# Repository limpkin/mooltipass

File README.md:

Mooltipass Project Repository
=============================

This is the GitHub repository dedicated to the Mooltipass device family. It contains all the resources that were used and made for this community-driven product line since the project was first started back in December 2013.  
The Mooltipass Mini device is available for purchase <b><a href="https://www.tindie.com/products/stephanelec/mooltipass-mini-offline-password-keeper/">on our Tindie store</a></b>.  

What is the Mooltipass Project?
-------------------------------
With time, logins and passwords have become critical elements we need to remember to access the different websites and services we use daily. If we want to achieve good security, each of these credential sets should be unique.  
We therefore created the Mooltipass, a physical password keeper that remembers and encrypts your credentials so you don't have to. With this device, you can generate and safely store long and complex passwords. A personal PIN locked smartcard allows the decryption of your credentials and ensures that only you have access to them. Simply visit a website and the device will ask for your confirmation to enter your credentials when login is required.  
The Mooltipass is a standalone device connected through USB, is completely driver-less and is compatible with all major operating systems on PCs, Macs and Smartphones. It therefore is extremely simple to use our device: - Plug the Mooltipass to your computer/tablet/phone, no driver installation required.  
- Insert your smart card, unlock it with your PIN. Without the PIN, the card is useless.  
- Visit the website that needs a login. If using our browser plugin the Mooltipass asks your permission to send the stored name and password or asks you to save/generate new credentials if you are logging in for the first time.  
- If you are not using the browser plugin or logging in to something other than a web browser, you can manually tell MP to send the correct name and password. It will type it in for you, just like a keyboard. In this way, it can be used anywhere.    

Advantages over software-based solutions
----------------------------------------
A software-based password keeper uses a passphrase to decrypt a credentials database located inside a device (computer, smartphone...). As at a given moment, your passphrase and your database are stored inside your device's memory, a malicious program with access to both elements could <b><a href="http://thehackernews.com/2014/11/new-citadel-trojan-targets-your.html">compromise all your passwords at once</a></b>. In some cases, security flaws of software-based solutions can also lead to entire unencrypted databases being extracted by <b><a href="http://www.theregister.co.uk/2016/07/27/zero_day_hole_can_pwn_millions_of_lastpass_users_who_visit_a_site">visiting a simple website</a></b>.  
We therefore offer the following advantages:  
- **Stronger security**: we reduce the number of attack vectors by basically having our device type your passwords for you. 
- A **non-proprietary device**: as our product is open anyone can develop new tools for it. There will never be fees for the services we offer.  
- An **open-source platform**: all our source code can be viewed, allowing you to check that your credentials are only kept inside the device and not leaked to the outside  
- A **trusted platform**: as only our tested source code is running on the Mooltipass, there can't be any viruses or malicious programs compromising your stored credentials  

The Platform
------------
The Mooltipass is composed of the main device shown above and a smart card.  
On the device are stored your AES-256 encrypted credentials. The smart card is a read protected memory that needs a PIN code to unlock its contents (AES-256 key + a few websites credentials). As with your chip and pin card, too many tries will permanently lock the smart card.

The Firmware
------------
**We want the device to be as simple as possible.** Ideally, the end user shouldn't have to spend more than a few seconds to use its basic functionalities.  
A browser extension runs on the user's computer and sends the current website to the Mooltipass. When the user has to log in, the Mooltipass will light up and ask for confirmation to enter the credentials.

Data Safety
-----------
Safety is a primary concern for the Mooltipass development team, which is why we offer several **secure** ways to backup your credentials.  
The smart card containing the AES key used for encrypting the passwords can be **cloned** using the Mooltipass, copying its PIN code as well. The encrypted credentials stored in the Mooltipass internal flash can be **exported** to the official Mooltipass website or simply somewhere on your local computer.

A Brief History of Security Flaws and Breaches
----------------------------------------------
We often think that the devices and websites we use are exempt from security flaws.  
You may see **if one of your accounts has already been compromised** by visiting <b><a href="https://haveibeenpwned.com/">this website</a></b>.  
We also compiled a brief list of major security breaches and vulnerabilities found during the last few months: 
- 01/2018 <a href="https://yro.slashdot.org/story/18/01/29/182210/lenovos-fingerprint-scanner-can-be-bypassed-via-a-hardcoded-password">
Lenovo's Fingerprint Scanner Can Be Bypassed via a Hardcoded Password </a>
- 12/2017 <a href="https://it.slashdot.org/story/17/12/17/0329223/windows-10-bundled-a-password-manager-with-a-security-flaw">Windows 10 Bundled a Password Manager with a Security Flaw </a>
- 09/2017 <a href="https://arstechnica.com/information-technology/2017/09/bluetooth-bugs-open-billions-of-devices-to-attacks-no-clicking-required/">Billions of devices imperiled by new clickless Bluetooth attack</a>
- 09/2017 <a href="https://techcrunch.com/2017/09/07/equifax-data-leak-could-involve-143-million-consumers/">Equifax data leak involves 143 million consumers</a>
- 08/2017 <a href="https://blog.quarkslab.com/vulnerabilities-in-high-assurance-boot-of-nxp-imx-microprocessors.html">Vulnerabilities in High Assurance Boot of NXP i.MX microprocessors</a>
- 08/2017 <a href="https://it.slashdot.org/story/17/08/01/206234/hackers-can-turn-amazon-echo-into-a-covert-listening-device">Hackers Can Turn Amazon Echo Into a Covert Listening Device</a>
- 07/2017 <a href="https://tech.slashdot.org/story/17/07/18/2039238/flaw-in-iot-security-cameras-leaves-millions-of-devices-open-to-hackers">Flaw In IoT Security Cameras Leaves Millions of Devices Open To Hackers</a>
- 07/2017 <a href="https://blog.exodusintel.com/2017/07/26/broadpwn/">**1 billion** smartphones can be compromised due to a flaw in BCM43XX chipsets</a>
- 07/2017 <a href="https://it.slashdot.org/story/17/07/03/0343258/severe-systemd-bug-allowed-remote-code-execution-for-two-years">Severe Systemd Bug Allowed Remote Code Execution For Two Years</a>
- 06/2017 <a href="https://it.slashdot.org/story/17/06/24/1825235/researcher-finds-critical-openvpn-bug-using-fuzzing">Researcher Finds Critical OpenVPN Bug Using Fuzzing</a>
- 06/2017 <a href="https://it.slashdot.org/story/17/06/23/1943245/wikileaks-doc-dump-reveals-cia-tools-for-hacking-air-gapped-pcs">WikiLeaks Doc Dump Reveals CIA Tools For Hacking Air-Gapped PCs</a>
- 06/2017 <a href="http://www.zdnet.com/article/zero-day-skype-flaw-causes-crashes-remote-code-execution/">Zero-day Skype flaw causes crashes, remote code execution</a>
- 06/2017 <a href="https://arstechnica.com/security/2017/06/advanced-cia-firmware-turns-home-routers-into-covert-listening-posts/">Advanced CIA firmware has been infecting Wi-Fi routers for years</a>
- 06/2017 <a href="http://www.zdnet.com/article/onelogin-hit-by-data-breached-exposing-sensitive-customer-data/">Password manager OneLogin hacked, exposing sensitive customer data</a>
- 05/2017 <a href="http://www.zdnet.com/pictures/biggest-hacks-leaks-and-data-breaches-2017/2/">2017 biggest hacks: Bell Canada, Edmodo, HipChat, Wonga, DaFont, PoliceOne hacked</a>
- 05/2017 <a href="http://www.wired.co.uk/article/kodi-vlc-subtitles-hack-risk-security">Kodi and VLC users at risk of viruses hidden in subtitles</a>
- 05/2017 <a href="https://hardware.slashdot.org/story/17/05/07/2034245/intels-remote-hijacking-flaw-was-worse-than-anyone-thought">Intel AMT bug that allows hackers to remotely gain administrative control over huge fleets of computers without entering a password</a>
- 03/2017 <a href="https://it.slashdot.org/story/17/03/19/0126257/edge-vmware-safari-and-ubuntu-linux-hacked-at-pwn2own-2017">Edge, VMWare, Safari, And Ubuntu Linux Hacked at Pwn2Own 2017</a>
- 03/2017 <a href="https://wikileaks.org/ciav7p1/">Vault 7: CIA Hacking Tools Revealed</a> : "These techniques permit the CIA to bypass the encryption of WhatsApp, Signal, Telegram, Wiebo, Confide and Cloackman by hacking the "smart" phones that they run on and collecting audio and message traffic before encryption is applied."
- 03/2017 <a href="https://it.slashdot.org/story/17/03/06/1838223/huge-database-leak-reveals-137-billion-email-addresses-and-exposes-illegal-spam-operation">Huge Database Leak Reveals 1.37 Billion Email Addresses and Exposes Illegal Spam Operation</a>
- 02/2017 <a href="https://it.slashdot.org/story/17/02/24/0319243/cloudflare-leaks-sensitive-user-data-across-the-web">Cloudflare Leaks Sensitive User Data Across the Web</a>
- 01/2017 <a href="https://www.schneier.com/blog/archives/2017/02/cryptkeeper_bug.html">Cryptkeeper Bug: the single-character decryption key "p" decrypts everything</a>
- 01/2017 <a href="https://it.slashdot.org/story/17/01/31/1425259/netgear-exploit-found-in-31-models-lets-hackers-turn-your-router-into-a-botnet">Netgear Exploit Found in 31 Models Lets Hackers Turn Your Router Into a Botnet</a>
- 01/2017 <a href="http://arstechnica.co.uk/security/2017/01/google-plugs-severe-android-bootmode-vulnerability/">Google plugs severe Android bootmode vuln that exposed devices to spying</a>
- 12/2016 <a href="https://linux.slashdot.org/story/16/12/16/0229207/zero-days-hitting-fedora-and-ubuntu-open-desktops-to-a-world-of-hurt">Zero-Days Hitting Fedora and Ubuntu Open Desktops To a World of Hurt </a>
- 12/2016 <a href="https://techcrunch.com/2016/12/14/yahoo-discloses-hack-of-1-billion-accounts/">Yahoo discloses hack of 1 billion accounts</a>
- 12/2016 <a href="https://it.slashdot.org/story/16/12/13/1611243/malware-found-in-the-firmware-of-26-low-cost-android-models">Malware Found In the Firmware of 26 Low-Cost Android Models </a>
- 11/2016 <a href="https://tech.slashdot.org/story/16/11/30/1720202/more-than-1-million-android-devices-rooted-by-gooligan-malware">More Than 1 Million Android Devices Rooted By Gooligan Malware</a>
- 11/2016 <a href="https://it.slashdot.org/story/16/11/20/0043259/second-chinese-firm-in-a-week-found-hiding-a-backdoor-in-android-firmware">Second Chinese Firm In a Week Found Hiding a Backdoor In Android Firmware </a>
- 10/2016 <a href="https://news.slashdot.org/story/16/10/24/2232220/rowhammer-attack-can-now-root-android-devices">Rowhammer Attack Can Now Root Android Devices</a>
- 10/2016 <a href="https://it.slashdot.org/story/16/10/24/1356255/china-electronics-firm-to-recall-some-us-products-after-hacking-attack">China Electronics Firm To Recall Some US Products After Hacking Attack </a>
- 10/2016 <a href="https://news.slashdot.org/story/16/10/13/2059232/android-devices-that-contain-foxconn-firmware-may-have-a-secret-backdoor">Android Devices That Contain Foxconn Firmware May Have a Secret Backdoor </a>
- 09/2016 <a href="https://it.slashdot.org/story/16/09/26/1942208/as-we-speak-teen-social-site-is-leaking-millions-of-plaintext-passwords">As We Speak, Teen Social Site Is Leaking Millions Of Plaintext Passwords </a>
- 09/2016 <a href="https://it.slashdot.org/story/16/09/22/095255/yahoo-confirms-massive-data-breach-500-million-users-impacted-updated">Yahoo Confirms Massive Data Breach, 500 Million Users Impacted</a>  
- 09/2016 <a href="https://yro.slashdot.org/story/16/09/24/0548206/97-of-the-top-companies-have-leaked-credentials-online">97% of the Top Companies Have Leaked Credentials Online</a>  
- 09/2016 <a href="https://it.slashdot.org/story/16/09/26/1942208/as-we-speak-teen-social-site-is-leaking-millions-of-plaintext-passwords">As We Speak, Teen Social Site Is Leaking Millions Of Plaintext Passwords</a>  
- 06/2016 <a href="http://www.independent.co.uk/life-style/gadgets-and-tech/news/ios-933-iphone-users-urged-to-update-after-apple-fixes-huge-password-vulnerability-a7149851.html">iOS bug allows attackers to gain full remote access to an iPhone by sending a simple iMesssage</a>  
- 06/2016 <a href="http://www.theregister.co.uk/2016/06/01/teamviewer_mass_breach_report/">Teamviewer hacked, users' Paypal account drained</a>  
- 06/2016 <a href="https://yro.slashdot.org/story/16/06/16/2035205/github-presses-big-red-password-reset-button-after-third-party-breach">GitHub Presses Big Red Password Reset Button After Third-Party Breach </a>  
- 05/2016 <a href="https://it.slashdot.org/story/16/05/27/1845202/hackers-claim-to-have-427-million-myspace-passwords">Hackers Claim to Have 427 Million Myspace Passwords</a>  
- 05/2016 <a href="https://it.slashdot.org/story/16/05/30/1227252/hackers-stole-65-million-passwords-from-tumblr">Hackers Stole 65 Million Passwords From Tumblr</a>  
- 06/2016 <a href="https://techcrunch.com/2016/06/08/twitter-hack/">Passwords for 32M Twitter accounts may have been hacked and leaked</a>  
- 06/2016 <a href="https://bits-please.blogspot.fr/2016/06/extracting-qualcomms-keymaster-keys.html">Android Full Disk Encryption Can Be Broken</a>  
- 07/2016 <a href="https://labs.bitdefender.com/2016/07/new-mac-backdoor-nukes-os-x-systems/">New Backdoor Allows Full Access to Mac Systems</a>  
- 08/2016 <a href="http://arstechnica.com/security/2016/08/qualcomm-chip-flaws-expose-900-million-android-devices/">Qualcomm security flaw allows a malicious app to gain root access</a>  
- 06/2016 <a href="https://it.slashdot.org/story/16/08/13/0325204/new-cache-attack-can-monitor-keystrokes-on-android-phones">New Cache Attack Can Monitor Keystrokes On Android Phones </a>  
- 03/2016 <a href="https://bogner.sh/2016/03/mitm-attack-against-keepass-2s-update-check/">MitM Attack against KeePass 2’s Update Check</a>  
- 07/2016 <a href="https://it.slashdot.org/story/16/07/08/2011205/apple-devices-held-for-ransom-rumors-claim-40m-icloud-accounts-hacked-apple-related-forums-compromised">Rumors Claim 40M iCloud Accounts Hacked; Apple-Related Forums Compromised</a>  
- 06/2016 <a href="http://www.theregister.co.uk/2016/07/27/zero_day_hole_can_pwn_millions_of_lastpass_users_who_visit_a_site/">Lastpass: remote 'complete account compromise' possible</a>  
- 08/2016 <a href="http://mashable.com/2016/08/26/iphone-malware-platform-secure">iPhone malware that steals your data is a reminder no platform is ever safe</a>  

Frequently Asked Questions
--------------------------

**Is your solution better than a piece of paper?**  
A piece of paper contains passwords that can easily be read when you are not paying attention to it. The Mooltipass stores encrypted passwords that can only be read when providing your PIN code.  

**If I only need to remember a PIN code, does it mean the Mooltipass is not safe?**  
Not at all, as the Mooltipass system is exactly like your chip and pin card: 3 false tries will permanently block the smart card and make credential decryption impossible.  

**Why do I need different passwords for different websites?**  
Web sites are compromised on a daily basis. If you are using the same password for different websites, one attacker could use a password he discovered on all of them.

**Why do you need an OLED screen?**  
An offline password keeper needs to provide a way to prevent *impersonation*. The user has to check that the website/service he's approving the credential sending for is the same that the website/service he's currently visiting/using, as a malicious program could emit forged requests. Moreover, having a display allows the user to operate the Mooltipass without the browser plugin using our dedicated touch interface.  
  
**Why are you using both a smart card and a main Mooltipass device?**  
There are many reasons, the main one being that it is much easier to carry a smart card around than any other object. This smart card is a secure element that contains your credentials' encryption key, it is cheap and may be cloned without compromising the system security.   
  
**What if I lose my smartcard?**  
Our device is shipped with two smart cards, so you can keep your copy somewhere safe. The Mooltipass, therefore, allows the user to clone his smartcard as many times as he wants, provided that the card PIN is correctly entered.  

**Can the smart card be used with multiple Mooltipass?**  
You can synchronize your credentials between multiple devices. This allows you to have one Mooltipass at work and one at home.  
  
**What if I lose my Mooltipass device?**  
Your encrypted credentials can be exported to either your computer or the Mooltipass official website. If you lose your device, you may purchase another one and restore your credentials.  

**Are you sure about your encryption implementation?**  
The AES-256 used in the Mooltipass has been compared again standard Nessie test vectors for correctness. Moreover, our security chain has been checked by qualified individuals.  
  
**Can I use it on Windows/Linux/Mac?**  
Yes, as no drivers are required to use the Mooltipass. It is recognized as a standard USB keyboard that will enter passwords for you.    
**Can I use on my computer/laptop/phone/tablet...?**  
Most (if not all) devices (including smartphones and tablet PCs) include a USB host capable port. The Mooltipass will work with all of them.  

**How secure is the Mooltipass?**  
We are using the most secure encryption algorithms and designed our case to make physical tampering practically impossible. Our solution is therefore perfectly suited for individuals wanting to improve their credentials safety.  

**Are you planning to make a wireless version?**  
The Mooltipass isn't wireless to skip the added costs of a lithium-ion battery and a wireless interface. Customer survey also let us know that having a USB cable wasn't a problem for most use cases.  

**How are the credentials sent to the computer?**  
The Mooltipass is enumerated as a composite HID keyboard / HID proprietary device. The credentials are sent over the HID proprietary channel when using the browser plugin and over the keyboard channel when using the Mooltipass through its touch interface.

**Is it still possible to sniff the passwords sent over HID?**  
In theory yes. As mentioned in our project description the Mooltipass aims at reducing the number of attack vectors to a minimum: the device basically types your password as if you were doing it yourself. Perfect security could only be achieved by sharing dedicated secrets with every possible service and website... which is practically impossible to do.

**If I can export my encrypted credentials, does this mean someone could crack them?**  
In short, no. We are using AES-256 encryption in CTR mode, brute-forcing the encrypted credentials takes more than fifty years.  

**If it is open source, does it mean it is less secure?**  
Not at all. Having our code open source allows everyone to check our security implementation, which actually leads to a better code quality and more trust from our final users.

Contact us
----------
You may contact the development team via <a href="https://groups.google.com/forum/?hl=en#!forum/Mooltipass">the official Google group</a> or ask for support at support[at]themooltipass[dot]com

Thanks and Acknowledgement
--------------------------
None of this would have been possible without the help of many people located all over the globe.  
Here is a nonexhaustive list:
- Darran H. (graphics, plugin, comms, general development and more) - New Zealand
- Pierre C. (GUI, encryption implementation supervision, pen testing) - France
- Bjorn W. (GUI, graphics, wise man, project advisor) - Canada
- Raoul H. (cross-platform daemon, browser extensions - France
- Henryk P. (encryption implementation supervision) - Unknown
- Olivier G. (mechanics, project advisor) - Switzerland
- Josh W. (mechanics, plugin, fw supervision) - USA
- Eric E. (schematics & layout verification) - USA
- Mike N. (flash storage, node management) - USA
- Charles E. (legal, project advisor) - USA
- Miguel A. (AES encryption, RNG) - Spain
- Tom V. (part of USB) - South Africa
- Erik M. (IRC, general help) - USA
- Mikael A. (GUI, plugin) - Sweden
- Hans N. (general help) - Denmark

Device History
--------------
1) Mooltipass Standard  
You may find all the articles detailing the Mooltipass Standard different life steps using <a href="http://hackaday.com/tag/developed-on-hackaday/">this link</a>.  
Our <a href="https://www.indiegogo.com/projects/mooltipass-open-source-offline-password-keeper">crowdfunding campaign</a> achieved its goal by raising around $125k in December 2014.

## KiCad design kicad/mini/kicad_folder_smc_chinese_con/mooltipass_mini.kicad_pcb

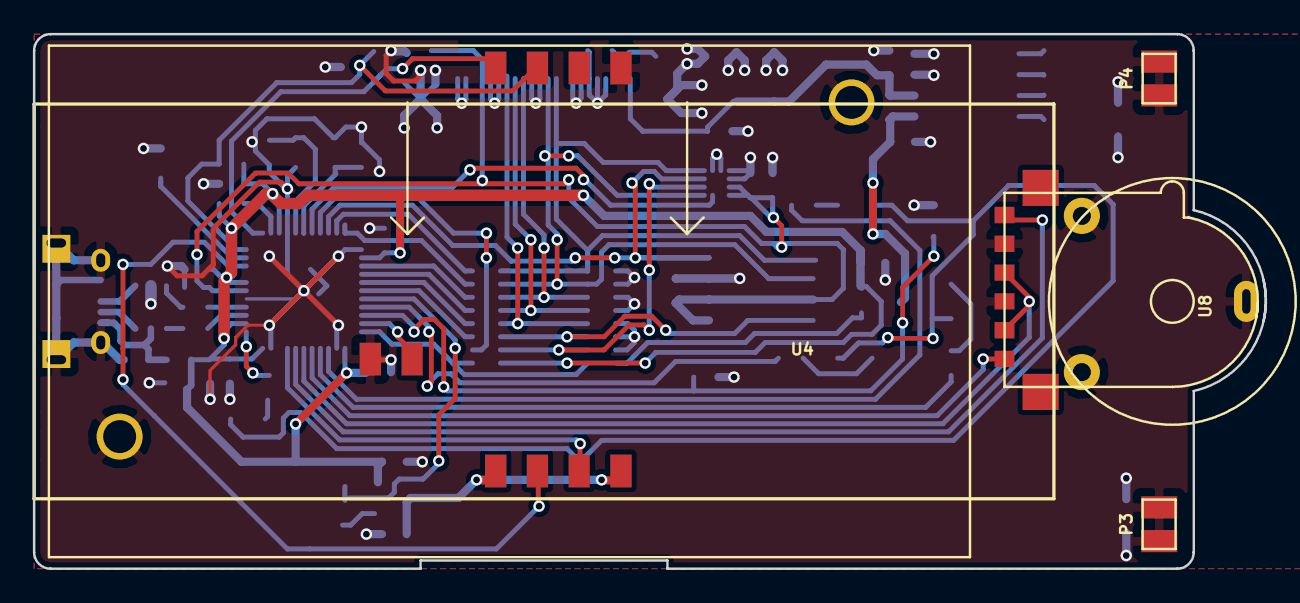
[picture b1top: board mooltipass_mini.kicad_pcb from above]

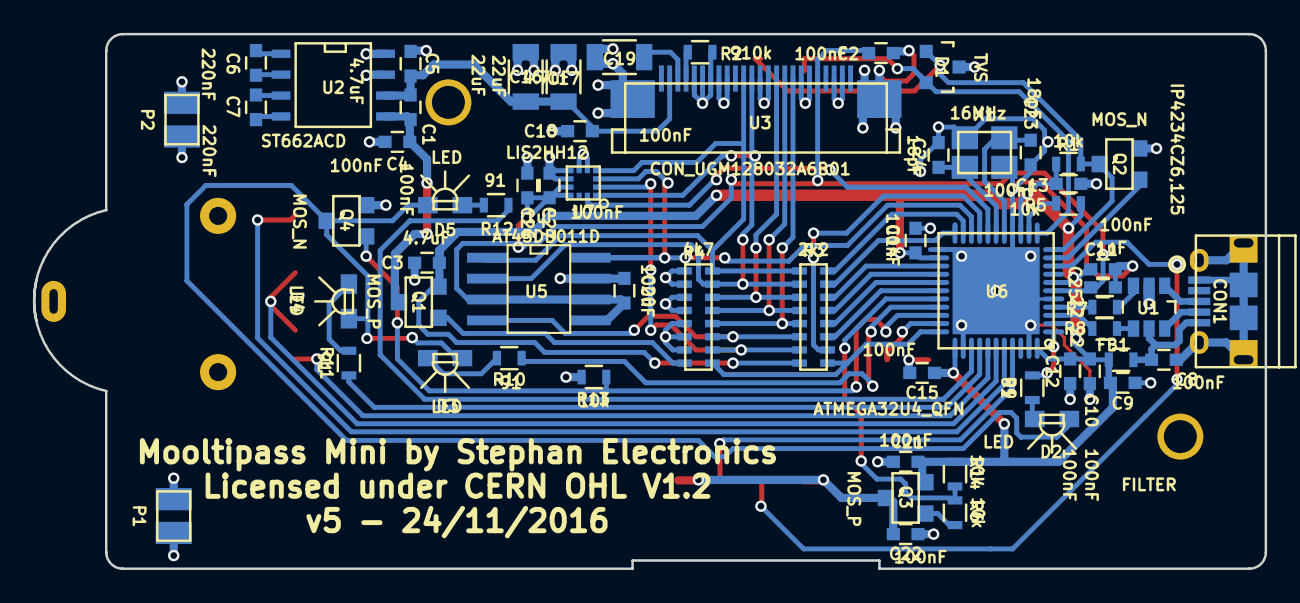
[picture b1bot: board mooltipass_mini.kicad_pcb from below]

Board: 2 copper layers, 74.9 x 32.5 mm, 65 parts (61 on the bottom side), 61 nets.

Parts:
C1, C2, C4, C8, C10, C11, C12, C13, C14, C15, C18, C20, C21, C22, C27: 100nF; C_0603
C3, C5, C9: 4.7uF; C_0603
C6, C7: 220nF; C_0603
C16, C17: 22uF; C_1206
C19: 4.7uF; C_1206
C23, C24: 18pF; C_0603
C25, C26: 1uF; C_0603
CON1: CON_10118194-0001LF; CONUSB_10118194
D1: TVS; SOT-23
D2, D3, D4, D5: LED; LTST-S220TBKT
FB1: FILTER; R_0603
P1, P2, P3, P4: EMC; EMC_SMR-TS-3-3-2DGR2E-01
Q1, Q3: MOS_P; SOT23-3
Q2, Q4: MOS_N; SOT23-3
R1, R5, R6, R13, R14: 10k; R_0603
R2: 910k; R_0603
R3: 2k2; RNETWORK8_0603
R4: 4k7; RNETWORK8_0603
R7, R8: 22; R_0603
R9, R10, R11, R12: 91; R_0603
U1: IP4234CZ6,125; TSOT-6-MK06A
U2: ST662ACD; SOIC-8-N
U3: CON_UGM128032A6B01; CON_SFV24R-2STE1HLF
U4: CON_SMARTCARD2; CON_SMARTCARD_CLONE_91-90473-003A
U5: AT45DB011D; SO8EN
U6: ATMEGA32U4_QFN; QFN44
U7: LIS2HH12; LGA-12
U8: TS005_WHEEL_CLICK; TS005_ENC_WHEEL_CLICK
X1: 16MHz; XTAL_3.2_2.5

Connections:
+3V3: C2.2, C20.1, C25.1, C26.1, C27.1, U3.5, U5.3, U5.5, U5.6, U6.6, U7.9, U7.10
+5V: C3.1, C9.1, C10.1, C11.1, C12.1, C13.1, C14.1, C15.1, C21.1, FB1.2, Q1.2, Q3.2, R1.1, R3.8, R5.2, R14.2, U6.2, U6.7, U6.14, U6.24, U6.34, U6.44
+12V: C1.1, C5.1, C16.1, C17.1, C18.1, U2.6, U3.23
/ACC_HV_SS: R3.10, U6.19
/ACC_INT: U6.18, U7.12
/ACC_SS: R3.7, R4.10, U7.2
/BL_POWER: Q1.1, R4.8
/DETECT_SC: U4.S1, U6.32
/ENC_A: U6.40, U8.A
/ENC_B: U6.38, U8.B
/ENC_SW: U6.39, U8.S1
/FLASH_HV_nS: R3.11, U6.28
/FLASH_nS: R3.6, R4.11, U5.4
/LCD_DnC: R3.3, R4.14, U3.10
/LCD_HV_DnC: R3.14, U6.25
/LCD_HV_SS: R3.12, U6.27
/LCD_HV_nRES: R3.13, U6.26
/LCD_SS: R3.5, R4.12, U3.8
/LCD_nRES: R3.4, R4.13, U3.9
/LED1: R9.1, U6.1
/LED2: R10.1, U6.30
/LED3: R11.1, U6.37
/LED4: R12.1, U6.36
/PWM_LED: Q4.1, R13.1, U6.31
/SC_IO: D1.1, Q2.3, R1.2, U4.C7, U6.11
/SC_PGM: D1.2, U4.C8, U6.12
/SC_POWER: R6.1, R14.1, U6.29
/SC_RST: U4.C2, U6.41
/SPI2_CLK: R3.2, R4.15, U3.13, U5.2, U7.1
/SPI2_HV_MOSI: R3.16, U6.21
/SPI2_HV_SCK: R3.15, U6.22
/SPI2_MISO: U5.8, U6.20, U7.3
/SPI2_MOSI: R3.1, R4.16, U3.14, U5.1, U7.4
/SPI_MOSI: Q2.1, U6.10
/SPI_SCK: U4.C3, U6.9
/USB_D+: R7.1, U1.3
/USB_D-: R8.1, U1.4
/VCC_SC: C22.1, Q3.3, U4.C1, U4.C4
/nRESET: R5.1, U6.13
GND: C2.1, C3.2, C4.2, C5.2, C8.2, C9.2, C10.2, C11.2, C12.2, C13.2, C14.2, C15.2, C16.2, C17.2, C18.2, C19.2, C20.2, C21.2, C22.2, C23.2, C24.2, C25.2, C26.2, C27.2, CON1.5, CON1.6, CON1.7, CON1.8, CON1.9, CON1.10, CON1.11, D1.3, P1.1, P2.1, P3.1, P4.1, Q2.2, Q4.2, R2.2, R4.1, R4.2, R4.3, R4.4, R4.5, R4.6, R4.7, R13.2, U1.2, U2.7, U2.8, U3.2, U3.3, U3.6, U3.7, U3.11, U3.12, U3.16, U3.17, U3.18, U3.19, U3.20, U3.25, U3.26, U4.C5, U4.FIX1, U4.FIX2, U4.S2, U5.7, U6.5, U6.15, U6.23, U6.35, U6.43, U6.45, U7.5, U7.6, U7.7, U7.8, U8.COM, U8.FIX3, U8.FIX4, U8.FIX5, U8.S2, X1.2, X1.4
unnamed: C1.2, C4.1, Q1.3, U2.5
unnamed: C6.1, U2.2
unnamed: C6.2, U2.1
unnamed: C7.1, U2.3
unnamed: C7.2, U2.4
unnamed: C19.1, U3.22
unnamed: C23.1, U6.16, X1.1
unnamed: C24.1, U6.17, X1.3
unnamed: CON1.2, U1.6
unnamed: CON1.3, U1.1
unnamed: D2.1, D3.1, D4.1, D5.1, Q4.3
unnamed: D2.2, R9.2
unnamed: D3.2, R10.2
unnamed: D4.2, R11.2
unnamed: D5.2, R12.2
unnamed: Q3.1, R6.2
unnamed: R2.1, U3.21
unnamed: R3.9, R4.9, U6.33
unnamed: R7.2, U6.4
unnamed: R8.2, U6.3
VCC: C8.1, CON1.1, FB1.1, U1.5

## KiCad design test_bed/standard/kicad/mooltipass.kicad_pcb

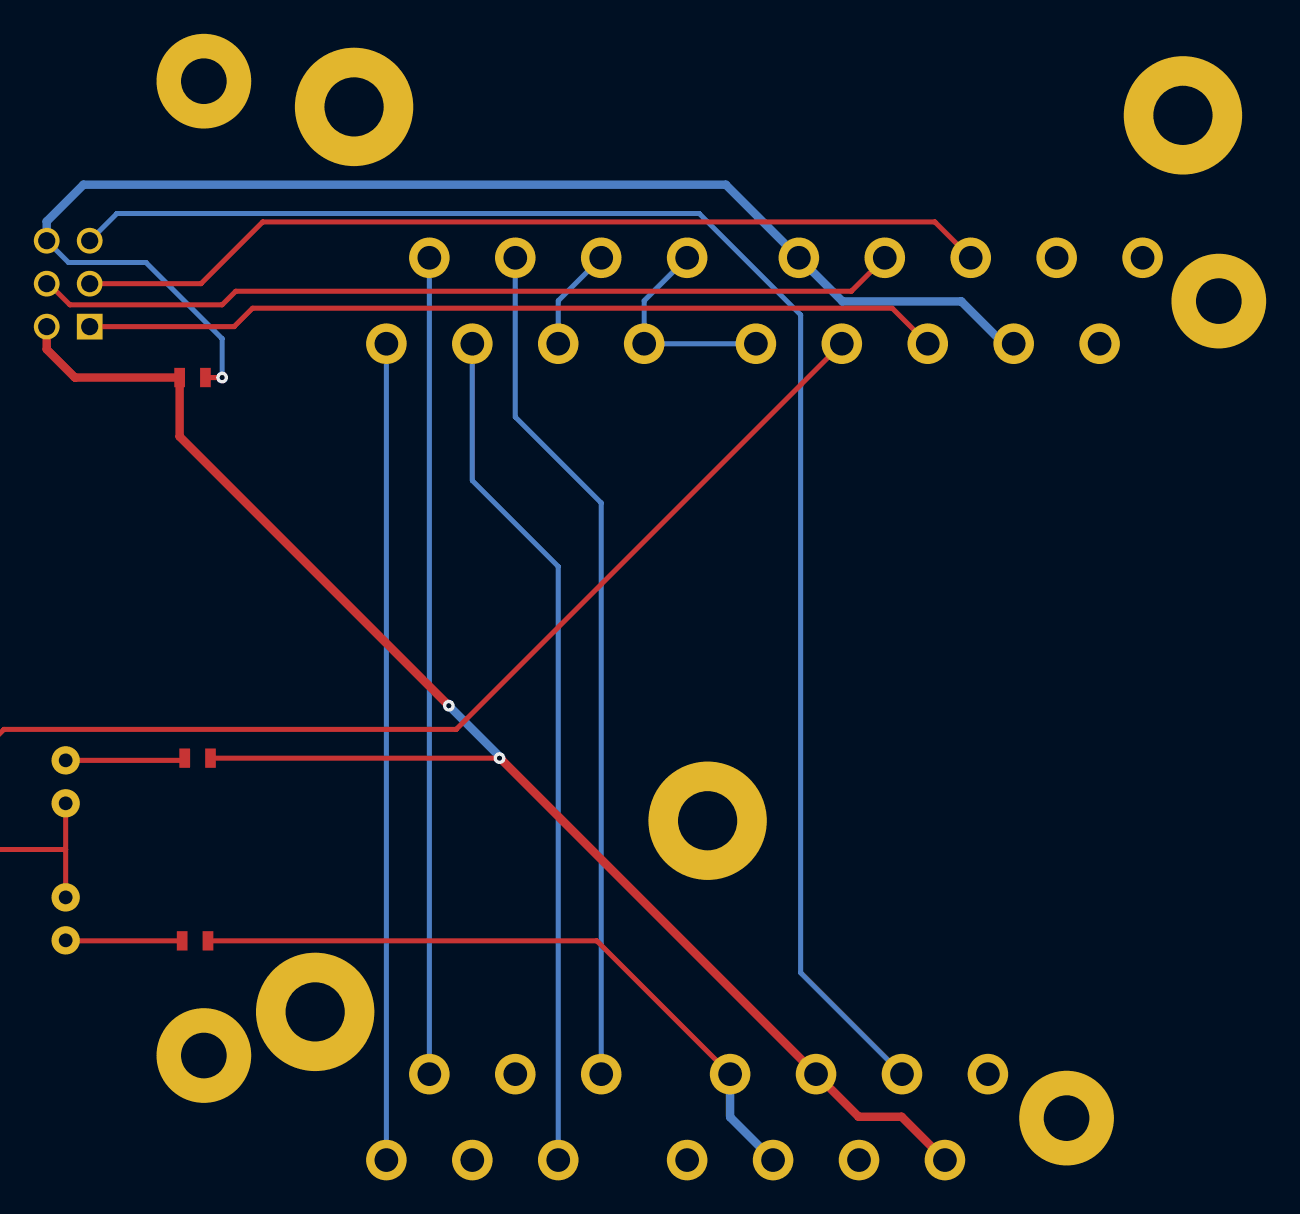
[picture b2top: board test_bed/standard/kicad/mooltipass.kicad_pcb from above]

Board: 2 copper layers, 18 parts (0 on the bottom side), 15 nets.

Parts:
C1: 100nF; SM0603
CON1: AVR-ISP-6; pin_array_3x2
D1: RED LED; LED-5MM
D2: GREEN LED; LED-5MM
P1, P4: CONN_8; CON_8_THROUGH_POGO
P2: CONN_6; CON_6_THROUGH_POGO
P3: CONN_10; CON_10_THROUGH_POGO
P5, P6, P7, P8: CONN_1; HOLE_FIX_M2.5_SMALL
P9, P10, P11, P12: CONN_1; HOLE_FIX_M3
R1, R2: 1k; SM0603_Resistor

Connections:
+5V: C1.1, CON1.2, P1.2, P1.5, R1.1
/I2C_SCL: P2.1, P3.1, P4.5
/I2C_SDA: P2.2, P3.2, P4.6
/PB4: P3.10, P4.1, P4.2
/PB6: D1.2, D2.1, P3.8
/PC6: P4.3, P4.4
/PD2: P2.6, P4.8
/PD3: P2.5, P4.7
/SPI_MISO: CON1.1, P3.6
/SPI_MOSI: CON1.4, P3.7
/SPI_SCK: CON1.3, P3.5
/nRESET: CON1.5, P1.3
GND: C1.2, CON1.6, P1.6, P1.7, P3.4, P3.9, R2.2
unnamed: D1.1, R1.2
unnamed: D2.2, R2.1

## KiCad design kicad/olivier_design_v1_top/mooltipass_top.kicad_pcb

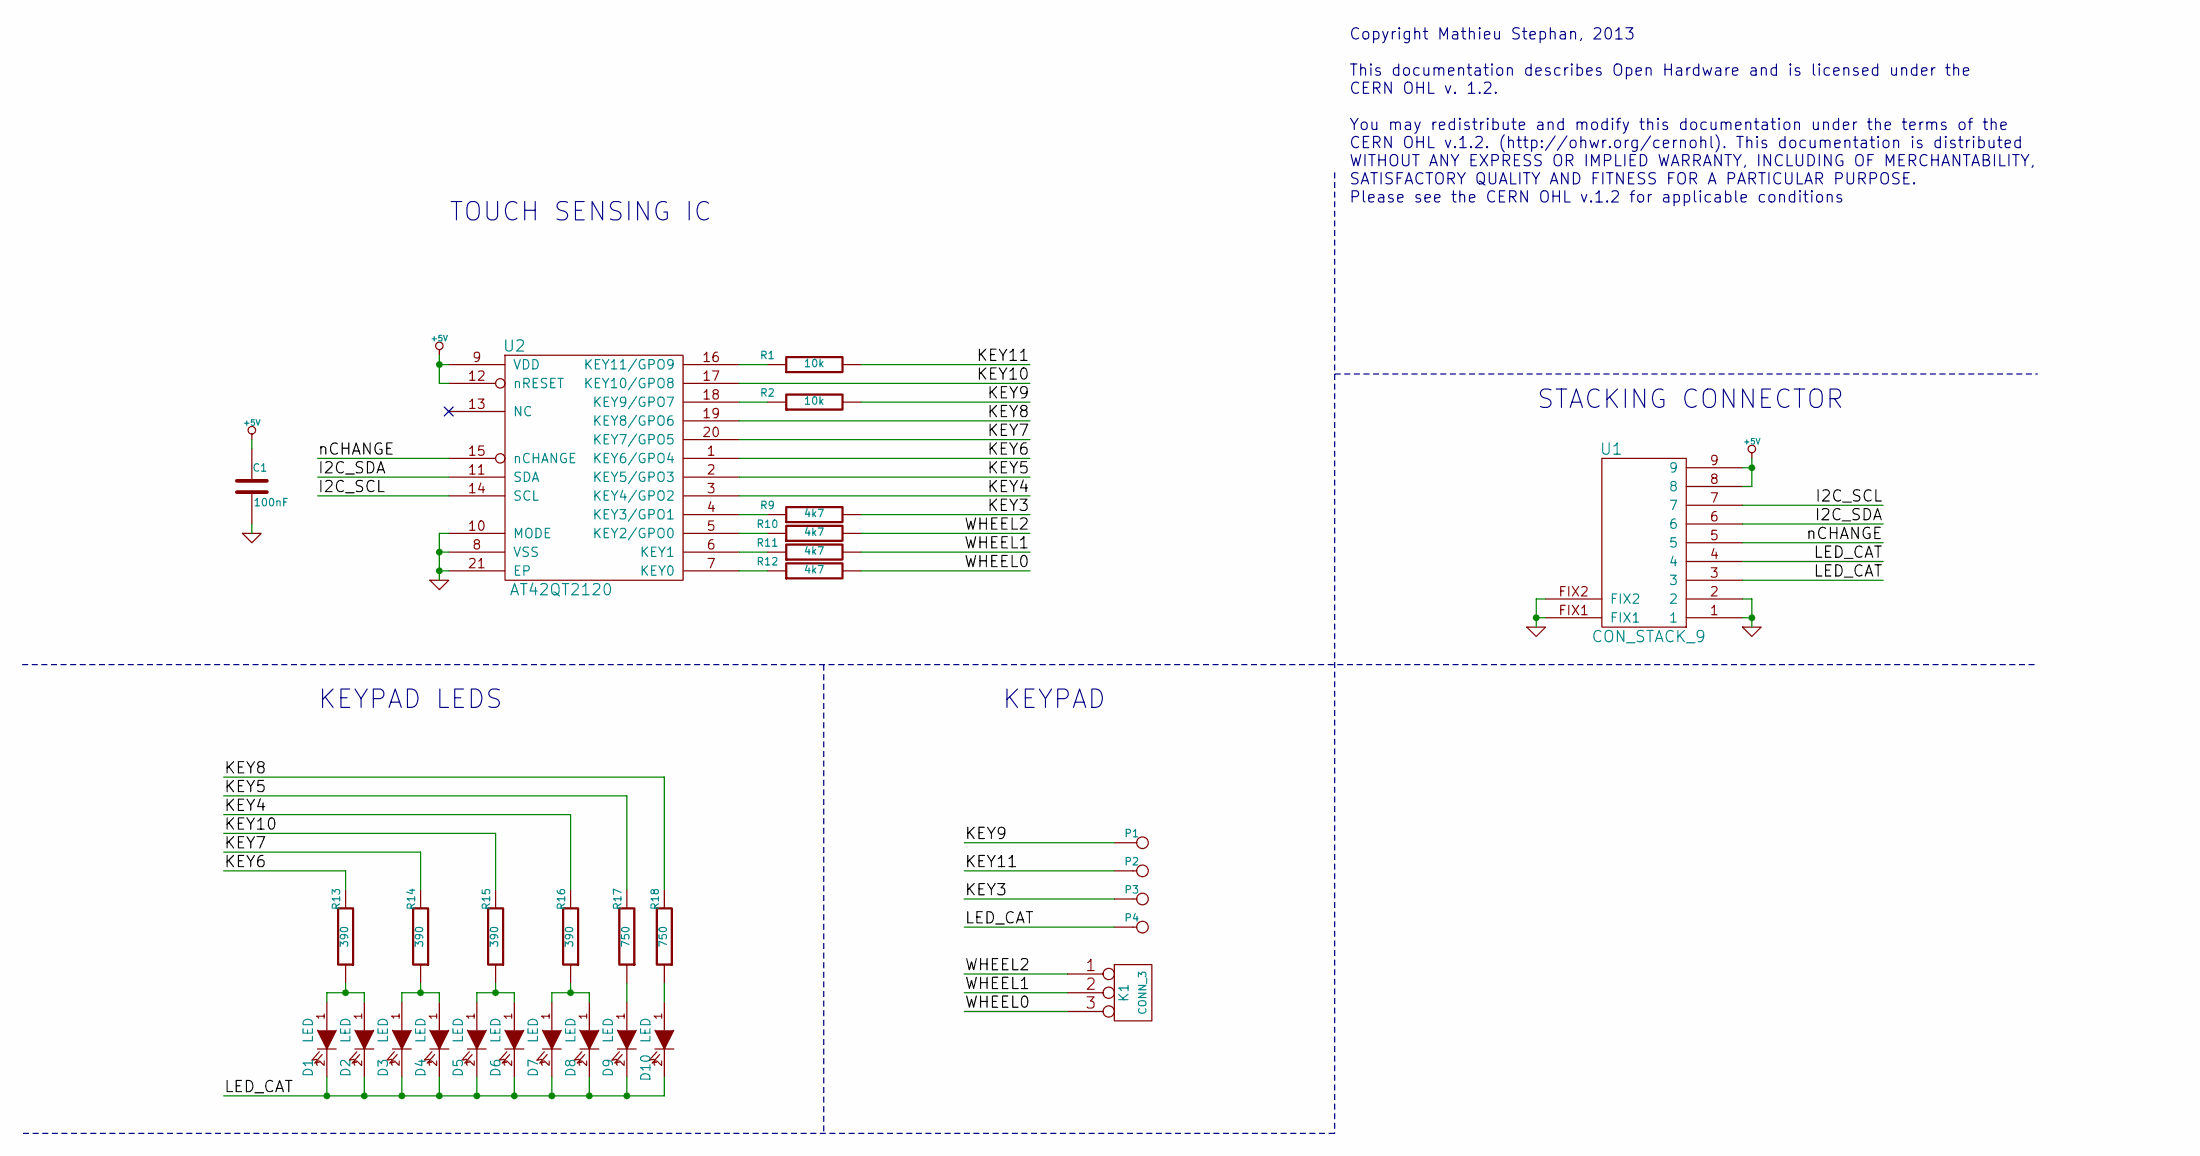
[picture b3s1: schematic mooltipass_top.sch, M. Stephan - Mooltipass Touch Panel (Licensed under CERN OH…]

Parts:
C1: 100nF
D1, D2, D3, D4, D5, D6, D7, D8, D9, D10: LED
K1: CONN_3
P1, P2, P3, P4: CONN_1
R1, R2: 10k
R9, R10, R11, R12: 4k7
R13, R14, R15, R16: 390
R17, R18: 750
U1: CON_STACK_9
U2: AT42QT2120

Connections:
+5V: C1.1, U1.8, U1.9, U2.9 (VDD), U2.12 (nRESET)
/I2C_SCL: U1.7, U2.14 (SCL)
/I2C_SDA: U1.6, U2.11 (SDA)
/KEY3: P3.1, R9.2
/KEY4: R16.2, U2.3 (KEY4/GPO2)
/KEY5: R17.2, U2.2 (KEY5/GPO3)
/KEY6: R13.2, U2.1 (KEY6/GPO4)
/KEY7: R14.2, U2.20 (KEY7/GPO5)
/KEY8: R18.2, U2.19 (KEY8/GPO6)
/KEY9: P1.1, R2.2
/KEY10: R15.2, U2.17 (KEY10/GPO8)
/KEY11: P2.1, R1.2
/LED_CAT: D1.2 (K), D2.2 (K), D3.2 (K), D4.2 (K), D5.2 (K), D6.2 (K), D7.2 (K), D8.2 (K), D9.2 (K), D10.2 (K), P4.1, U1.3, U1.4
/WHEEL0: K1.3, R12.2
/WHEEL1: K1.2 (PM), R11.2
/WHEEL2: K1.1, R10.2
/nCHANGE: U1.5, U2.15 (nCHANGE)
GND: C1.2, U1.1, U1.2, U1.FIX1, U1.FIX2, U2.8 (VSS), U2.10 (MODE), U2.21 (EP)
unnamed: D3.1 (A), D4.1 (A), R14.1
unnamed: D5.1 (A), D6.1 (A), R15.1
unnamed: D7.1 (A), D8.1 (A), R16.1
unnamed: D1.1 (A), D2.1 (A), R13.1
unnamed: R2.1, U2.18 (KEY9/GPO7)
unnamed: D9.1 (A), R17.1
unnamed: D10.1 (A), R18.1
unnamed: R11.1, U2.6 (KEY1)
unnamed: R12.1, U2.7 (KEY0)
unnamed: R10.1, U2.5 (KEY2/GPO0)
unnamed: R9.1, U2.4 (KEY3/GPO1)
unnamed: R1.1, U2.16 (KEY11/GPO9)

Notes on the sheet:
Copyright Mathieu Stephan, 2013 This documentation describes Open Hardware and is licensed under the CERN OHL v. 1.2. You may redistribute and modify this documentation under the terms of the CERN OHL v.1.2. (http://ohwr.org/cernohl). This documentation is distributed WITHOUT ANY EXPRESS OR IMPLIED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
TOUCH SENSING IC
STACKING CONNECTOR
KEYPAD LEDS
KEYPAD

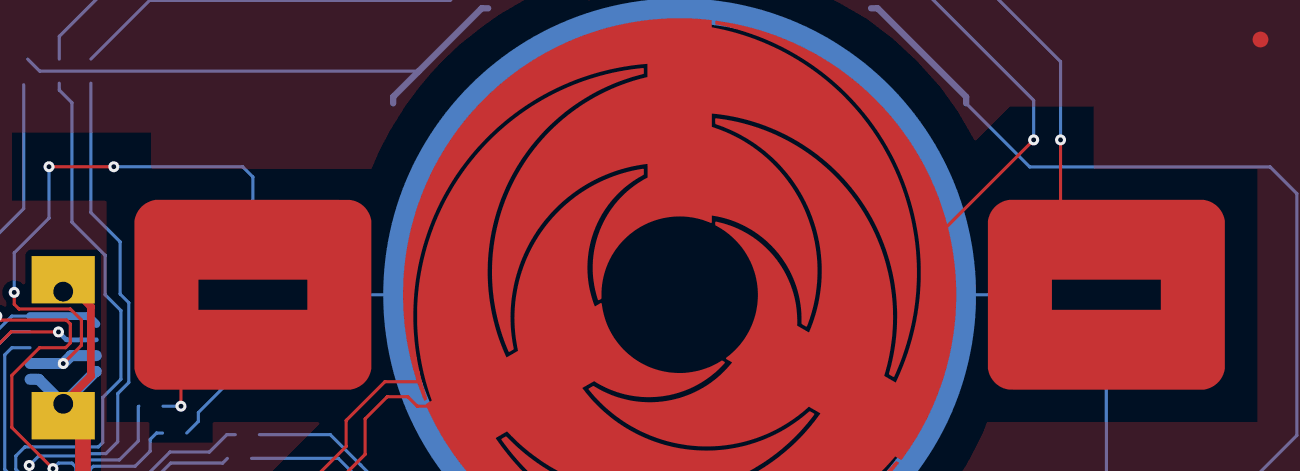
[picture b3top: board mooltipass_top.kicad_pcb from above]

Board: 2 copper layers, 32 parts (0 on the bottom side), 30 nets.

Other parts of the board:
VAL: soldermask_light
VAL#2: REF; mooltipass_top_slot_drill

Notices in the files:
kicad/mini/kicad_folder_smc_chinese_con/mooltipass_mini.kicad_pcb:
Licensed under CERN OHL V1.2
kicad/olivier_design_v1/mooltipass.sch:
M. Stephan - Offline Password Keeper Schematics (Licensed under CERN OHL V1.2)
kicad/olivier_design_v1_for_prod/mooltipass.sch:
M. Stephan - Mooltipass Schematics (Licensed under CERN OHL V1.2)
kicad/olivier_design_v1_top/mooltipass_top.sch:
M. Stephan - Mooltipass Touch Panel (Licensed under CERN OHL V1.2)
test_bed/standard/kicad/mooltipass.sch:
M. Stephan - Test Bed Schematics (Licensed under CERN OHL V1.2)
